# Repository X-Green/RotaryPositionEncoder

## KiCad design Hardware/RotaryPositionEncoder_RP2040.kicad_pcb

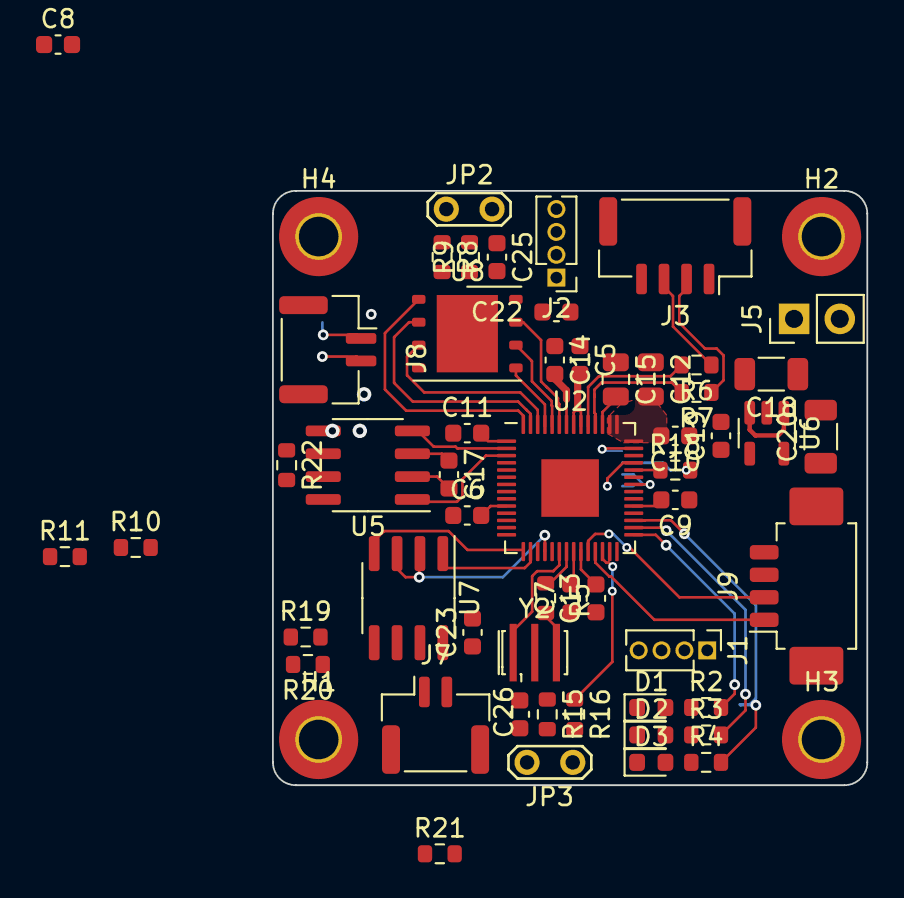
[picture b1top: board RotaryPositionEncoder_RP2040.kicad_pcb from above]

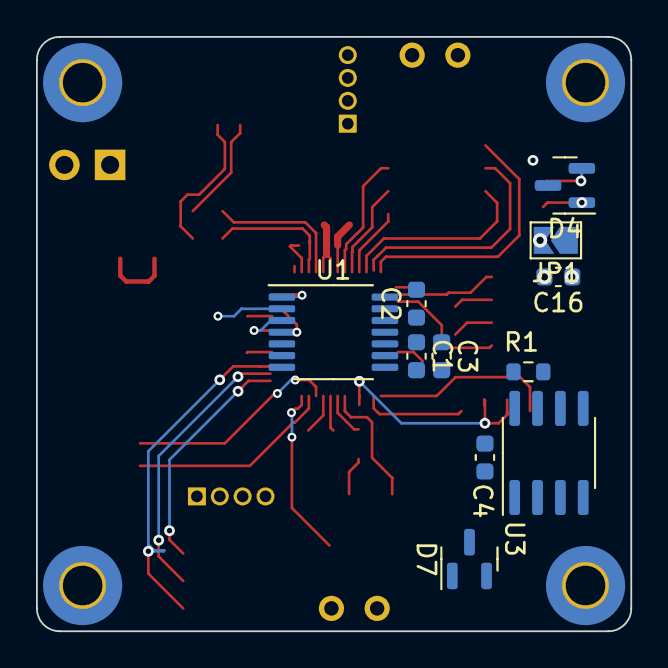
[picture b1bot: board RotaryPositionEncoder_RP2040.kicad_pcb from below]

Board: 4 copper layers, 33.0 x 33.0 mm, 69 parts (11 on the bottom side), 54 nets.

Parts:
C1, C4, C5, C6, C7, C8, C9, C10, C11, C13, C14, C16, C17, C22, C23, C25: 100nF; C_0603_1608Metric
C2: 2.2uF; C_0603_1608Metric
C3, C26: 1uF; C_0603_1608Metric
C12, C15: 2.2uF; C_0805_2012Metric
C18: 10uF; C_1206_3216Metric
C19: 10nF; C_0603_1608Metric
C20: 2.2uF; C_1206_3216Metric
D1, D2, D3: LED; LED_0603_1608Metric
D4, D7: NUP2105L; SOT-23
H1, H2, H3, H4: MountingHole_Pad; MountingHole_2.2mm_M2_Pad_TopBottom
J1: Conn_ABI; PinHeader_1x04_P1.27mm_Vertical
J2: Conn_UVW; PinHeader_1x04_P1.27mm_Vertical
J3: Conn_USB; JST_GH_SM04B-GHS-TB_1x04-1MP_P1.25mm_Horizontal
J5: Conn_5VDC; PinHeader_1x02_P2.54mm_Vertical
J7, J8: Conn_CAN; JST_GH_SM02B-GHS-TB_1x02-1MP_P1.25mm_Horizontal
J9: Conn_01x04_MountingPin; Molex_PicoBlade_53261-0471_1x04-1MP_P1.25mm_Horizontal
JP1: SolderJumper_2_Open; SolderJumper-2_P1.3mm_Open_TrianglePad1.0x1.5mm
JP2, JP3: Jumper_2_Open; TestPoint_2Pads_Pitch2.54mm_Drill0.8mm
R1: DNF; R_0603_1608Metric
R2, R3, R4, R10, R11: 4.7K; R_0603_1608Metric
R5: 470R; R_0603_1608Metric
R6, R7: 27.4R; R_0603_1608Metric
R8, R16: 1K; R_0603_1608Metric
R9, R15: 10K; R_0603_1608Metric
R18: 33R; R_0603_1608Metric
R19, R20: 536R; R_0603_1608Metric
R21, R22: 120R; R_0603_1608Metric
U1: AS5047P; TSSOP-14_4.4x5mm_P0.65mm
U2: RP2040; QFN-56-1EP_7x7mm_P0.4mm_EP3.2x3.2mm
U3: M24C02-RMN; SOIC-8_3.9x4.9mm_P1.27mm
U5: TJA1042T; SOIC-8_3.9x4.9mm_P1.27mm
U6: RT9013-33GB; TSOT-23-5
U7: MAX14783ExS; SOIC-8_3.9x4.9mm_P1.27mm
U8: W25Q32JVZP; WSON-8-1EP_6x5mm_P1.27mm_EP3.4x4.3mm
Y2: Crystal_GND2; Resonator_SMD_Murata_CSTxExxV-3Pin_3.0x1.1mm_HandSoldering

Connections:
+3V3: C4.1, C5.2, C6.2, C7.2, C8.2, C9.2, C10.2, C11.2, C12.2, C20.1, C22.1, C25.2, C26.2, JP1.2 (B), R1.2, R9.1, R10.1, R11.1, R15.1, U2.1 (IOVDD), U2.10 (IOVDD), U2.22 (IOVDD), U2.33 (IOVDD), U2.42 (IOVDD), U2.43 (ADC_AVDD), U2.44 (VREG_IN), U2.48 (USB_VDD), U2.49 (IOVDD), U3.8 (VCC), U6.5 (VOUT), U8.8 (VCC)
+5V: C1.1, C3.1, C17.1, C18.1, C23.1, J3.1, J5.1, R19.2, U1.11 (VDD), U5.3 (VCC), U6.1 (VIN), U6.3 (EN), U7.8 (VCC)
/CAN_H: D4.1 (K), J8.2, R22.2, U5.7 (CANH)
/CAN_L: D4.2 (K), J8.1, R22.1, U5.6 (CANL)
/CAN_RX: U2.2 (GPIO0), U5.4 (RXD)
/CAN_TX: U2.3 (GPIO1), U5.1 (TXD)
/I2C_SCL: R11.2, U2.5 (GPIO3), U3.6 (SCL)
/I2C_SDA: R10.2, U2.4 (GPIO2), U3.5 (SDA)
/QSPI_CLK: U2.52 (QSPI_SCLK), U8.6 (CLK)
/QSPI_SD0: U2.53 (QSPI_SD0), U8.5 (DI(IO0))
/QSPI_SD1: U2.55 (QSPI_SD1), U8.2 (DO(IO1))
/QSPI_SD2: U2.54 (QSPI_SD2), U8.3 (IO2)
/QSPI_SD3: U2.51 (QSPI_SD3), U8.7 (IO3)
/QSPI_SS: R8.2, R9.2, U2.56 (QSPI_SS), U8.1 (~CS)
/RS485_A: D7.1 (K), J7.2, R19.1, R21.2, U7.6 (A)
/RS485_B: D7.2 (K), J7.1, R20.1, R21.1, U7.7 (B)
/RUN: R15.2, R16.1, U2.26 (RUN)
/SPI_CLK: R18.2, U1.2 (CLK)
/SPI_CS: U1.1 (~CS), U2.41 (GPIO29_ADC3)
/SPI_MISO: U1.3 (MISO), U2.36 (GPIO24)
/SPI_MOSI: U1.4 (MOSI), U2.39 (GPIO27_ADC1)
/UART_RTS: U2.18 (GPIO15), U7.2 (~RE), U7.3 (DE)
/UART_RX: U2.16 (GPIO13), U7.1 (RO)
/UART_TX: U2.15 (GPIO12), U7.4 (DI)
/USB_DM: J3.2, R7.1
/USB_DP: J3.3, R6.1
/VREG: C13.2, C14.2, C15.2, U2.23 (DVDD), U2.45 (VREG_VOUT), U2.50 (DVDD)
GND: C1.2, C2.2, C3.2, C4.2, C5.1, C6.1, C7.1, C8.1, C9.1, C10.1, C11.1, C12.1, C13.1, C14.1, C15.1, C16.2, C17.2, C18.2, C19.2, C20.2, C22.2, C23.2, C25.1, C26.1, D1.1 (K), D2.1 (K), D3.1 (K), D4.3 (A), D7.3 (A), J1.1, J2.1, J3.4, J3.MP (MountPin), J5.2, J7.MP (MountPin), J8.MP (MountPin), J9.3, JP2.1 (A), JP3.1 (A), R20.2, U1.5 (TST), U1.13 (GND), U2.19 (TESTEN), U2.57 (GND), U3.1 (E0), U3.2 (E1), U3.3 (E2), U3.4 (VSS), U5.2 (GND), U5.8 (STB), U6.2 (GND), U7.5 (GND), U8.4 (GND), U8.9 (EP), Y2.2
unnamed: D1.2 (A), R2.1
unnamed: D2.2 (A), R3.1
unnamed: D3.2 (A), R4.1
unnamed: J1.2, U1.14 (I/PWM)
unnamed: J1.3, U1.6 (B)
unnamed: J1.4, U1.7 (A)
unnamed: J2.2, U1.8 (W/PWM)
unnamed: J2.3, U1.9 (V)
unnamed: J2.4, U1.10 (U)
unnamed: J9.1, U2.25 (SWD)
unnamed: J9.2, U2.24 (SWCLK)
unnamed: C16.1, JP1.1 (A), U5.5 (SPLIT)
unnamed: JP2.2 (B), R8.1
unnamed: JP3.2 (B), R16.2
unnamed: R5.1, Y2.3
unnamed: C2.1, U1.12 (VDD3V3)
unnamed: R2.2, U2.29 (GPIO18)
unnamed: R3.2, U2.30 (GPIO19)
unnamed: R4.2, U2.31 (GPIO20)
unnamed: R18.1, U2.38 (GPIO26_ADC0)
unnamed: R7.2, U2.46 (USB_DM)
unnamed: R6.2, U2.47 (USB_DP)
unnamed: U2.20 (XIN), Y2.1
unnamed: R5.2, U2.21 (XOUT)
unnamed: R1.1, U3.7 (~WC)
unnamed: C19.1, U6.4 (SENSE/ADJ)

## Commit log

2023-02-20 init
2023-02-20 add docs
2023-02-27 schematic done
2023-02-27 sch modify pcb init
2023-03-13 add rs485
2023-03-13 fix: CAN/RS485 connector footprint change: TVS -> NUP2105 change: Flash SOP->WSOP
2023-03-13 Fix: RS485 Pullup/Pulldown Resistor
2023-03-15 Changed USB-C Plug into GH1.25 Connector to take less space
2023-03-16 Layout almost done Todo: Change QFN56 footprint into handsolder
2023-03-23 almost done pcb layout v1
